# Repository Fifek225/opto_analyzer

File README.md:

This is a project of a RaspberryPi Pico expander board for Optical power measurements.
SFP connector acts as a receiver (analysis) and transmitter (test signals) of optical impulses.
External attenuators can be used to "play" with the power level.

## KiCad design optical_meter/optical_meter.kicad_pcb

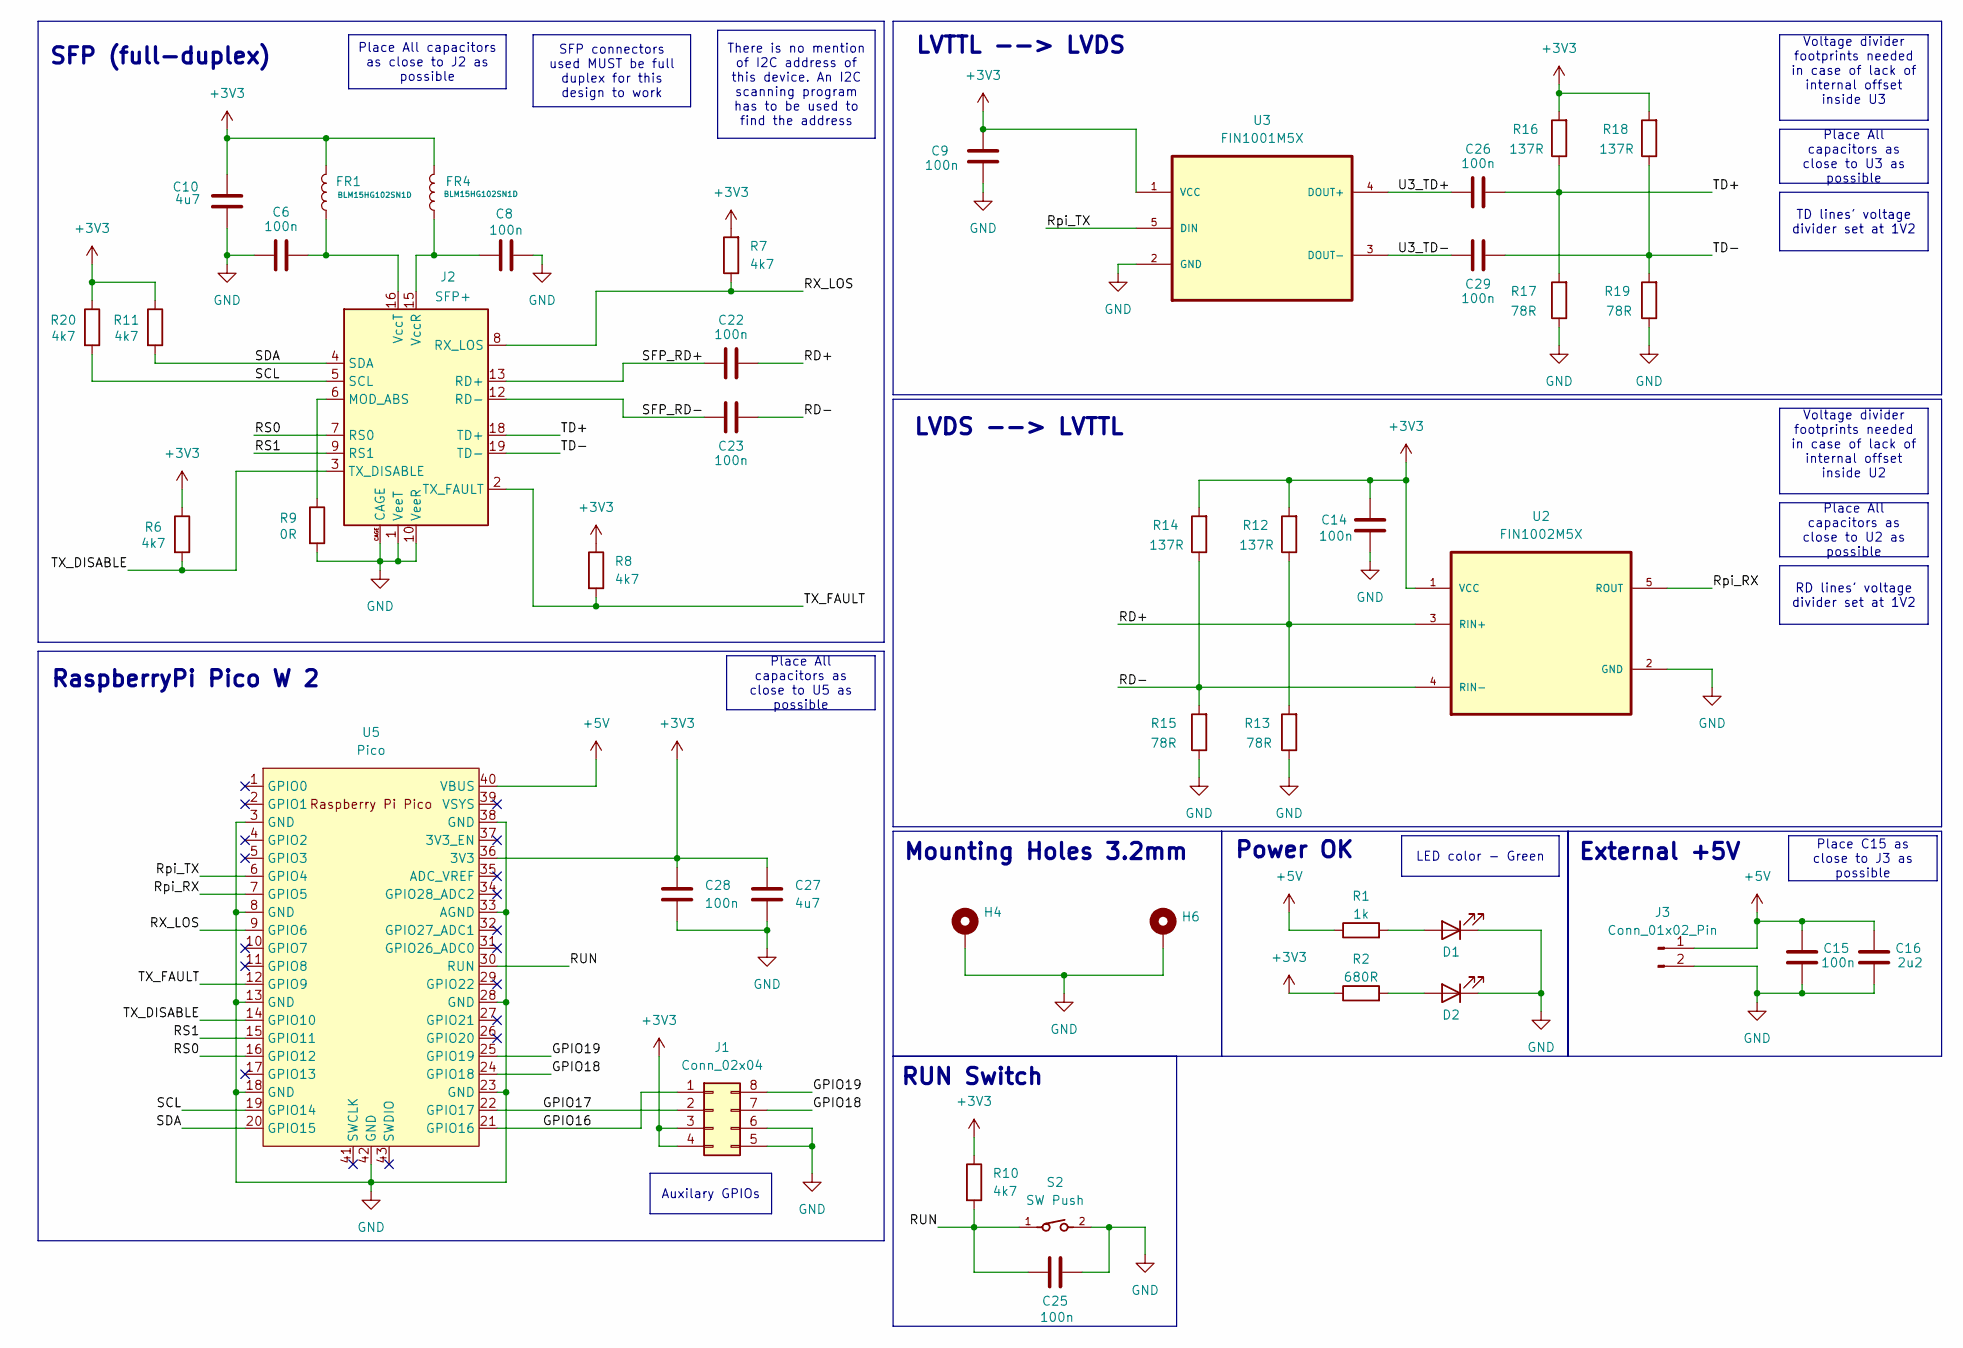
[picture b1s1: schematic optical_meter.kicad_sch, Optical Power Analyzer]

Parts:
C6, C8, C9, C14, C15, C22, C23, C25, C26, C28, C29: 100n; C_0603_1608Metric
C10, C27: 4u7; C_0603_1608Metric
C16: 2u2; C_0603_1608Metric
D1, D2: LED; LED_0603_1608Metric_Pad1.05x0.95mm_HandSolder
FR1, FR4: BLM15HG102SN1D; L_0402_1005Metric_Pad0.77x0.64mm_HandSolder
H4, H6: MountingHole_3.2mm_M3_DIN965_Pad
J1: Conn_02x04; PinHeader_2x04_P2.54mm_Vertical
J2: SFP+; Connector_SFP_and_Cage
J3: Conn_01x02_Pin; PinHeader_1x02_P2.54mm_Vertical
R1: 1k; R_0603_1608Metric_Pad0.98x0.95mm_HandSolder
R2: 680R; R_0603_1608Metric_Pad0.98x0.95mm_HandSolder
R6, R7, R8, R10, R11, R20: 4k7; R_0603_1608Metric_Pad0.98x0.95mm_HandSolder
R9: 0R; R_0603_1608Metric_Pad0.98x0.95mm_HandSolder
R12, R14, R16, R18: 137R; R_0603_1608Metric_Pad0.98x0.95mm_HandSolder
R13, R15, R17, R19: 78R; R_0603_1608Metric_Pad0.98x0.95mm_HandSolder
S2: SW Push; 434123025816
U2: FIN1002M5X; SOT95P280X140-5N; MPN FIN1002M5X
U3: FIN1001M5X; SOT95P280X140-5N; MPN FIN1001M5X
U5: Pico; RPi_Pico_SMD_TH

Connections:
+3V3: C9.2, C10.2, C14.1, C27.1, C28.1, FR1.2, FR4.2, J1.3, J1.4, R2.1, R6.1, R7.2, R8.1, R10.1, R11.1, R12.2, R14.2, R16.2, R18.2, R20.1, U2.1 (VCC), U3.1 (VCC), U5.36 (3V3)
+5V: C15.1, C16.1, J3.1, R1.1, U5.40 (VBUS)
/GPIO16: J1.1, U5.21 (GPIO16)
/GPIO17: J1.2, U5.22 (GPIO17)
/GPIO18: J1.7, U5.24 (GPIO18)
/GPIO19: J1.8, U5.25 (GPIO19)
/RD+: C22.2, R12.1, R13.2, U2.3 (RIN+)
/RD-: C23.2, R14.1, R15.2, U2.4 (RIN-)
/RS0: J2.7 (RS0), U5.16 (GPIO12)
/RS1: J2.9 (RS1), U5.15 (GPIO11)
/RUN: C25.2, R10.2, S2.1, U5.30 (RUN)
/RX_LOS: J2.8 (RX_LOS), R7.1, U5.9 (GPIO6)
/Rpi_RX: U2.5 (ROUT), U5.7 (GPIO5)
/Rpi_TX: U3.5 (DIN), U5.6 (GPIO4)
/SCL: J2.5 (SCL), R20.2, U5.19 (GPIO14)
/SDA: J2.4 (SDA), R11.2, U5.20 (GPIO15)
/SFP_RD+: C22.1, J2.13 (RD+)
/SFP_RD-: C23.1, J2.12 (RD-)
/TD+: C26.2, J2.18 (TD+), R16.1, R17.2
/TD-: C29.2, J2.19 (TD-), R18.1, R19.2
/TX_DISABLE: J2.3 (TX_DISABLE), R6.2, U5.14 (GPIO10)
/TX_FAULT: J2.2 (TX_FAULT), R8.2, U5.12 (GPIO9)
/U3_TD+: C26.1, U3.4 (DOUT+)
/U3_TD-: C29.1, U3.3 (DOUT-)
GND: C6.1, C8.2, C9.1, C10.1, C14.2, C15.2, C16.2, C25.1, C27.2, C28.2, D1.1 (K), D2.1 (K), H4.1, H6.1, J1.5, J1.6, J2.1 (VeeT), J2.10 (VeeR), J2.11 (VeeR), J2.14 (VeeR), J2.17 (VeeT), J2.20 (VeeT), J2.CAGE, J3.2, R9.2, R13.1, R15.1, R17.1, R19.1, S2.2, U2.2 (GND), U3.2 (GND), U5.3 (GND), U5.8 (GND), U5.13 (GND), U5.18 (GND), U5.23 (GND), U5.28 (GND), U5.33 (AGND), U5.38 (GND), U5.42 (GND); also elsewhere on the board
unnamed: D1.2 (A), R1.2
unnamed: D2.2 (A), R2.2
unnamed: J2.6 (MOD_ABS), R9.1
unnamed: C8.1, FR4.1, J2.15 (VccR)
unnamed: C6.2, FR1.1, J2.16 (VccT)

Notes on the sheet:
RUN Switch
Power OK
External +5V
LVTTL --> LVDS
Mounting Holes 3.2mm
RaspberryPi Pico W 2
LVDS --> LVTTL
SFP (full-duplex)
TD lines' voltage divider set at 1V2
Place All capacitors as close to J2 as possible
Place All capacitors as close to U2 as possible
Voltage divider footprints needed in case of lack of internal offset inside U3
Place All capacitors as close to U5 as possible
There is no mention of I2C address of this device. An I2C scanning program has to be used to find the address
Voltage divider footprints needed in case of lack of internal offset inside U2
Place C15 as close to J3 as possible
Auxilary GPIOs
SFP connectors used MUST be full duplex for this design to work
LED color - Green
Place All capacitors as close to U3 as possible
RD lines' voltage divider set at 1V2

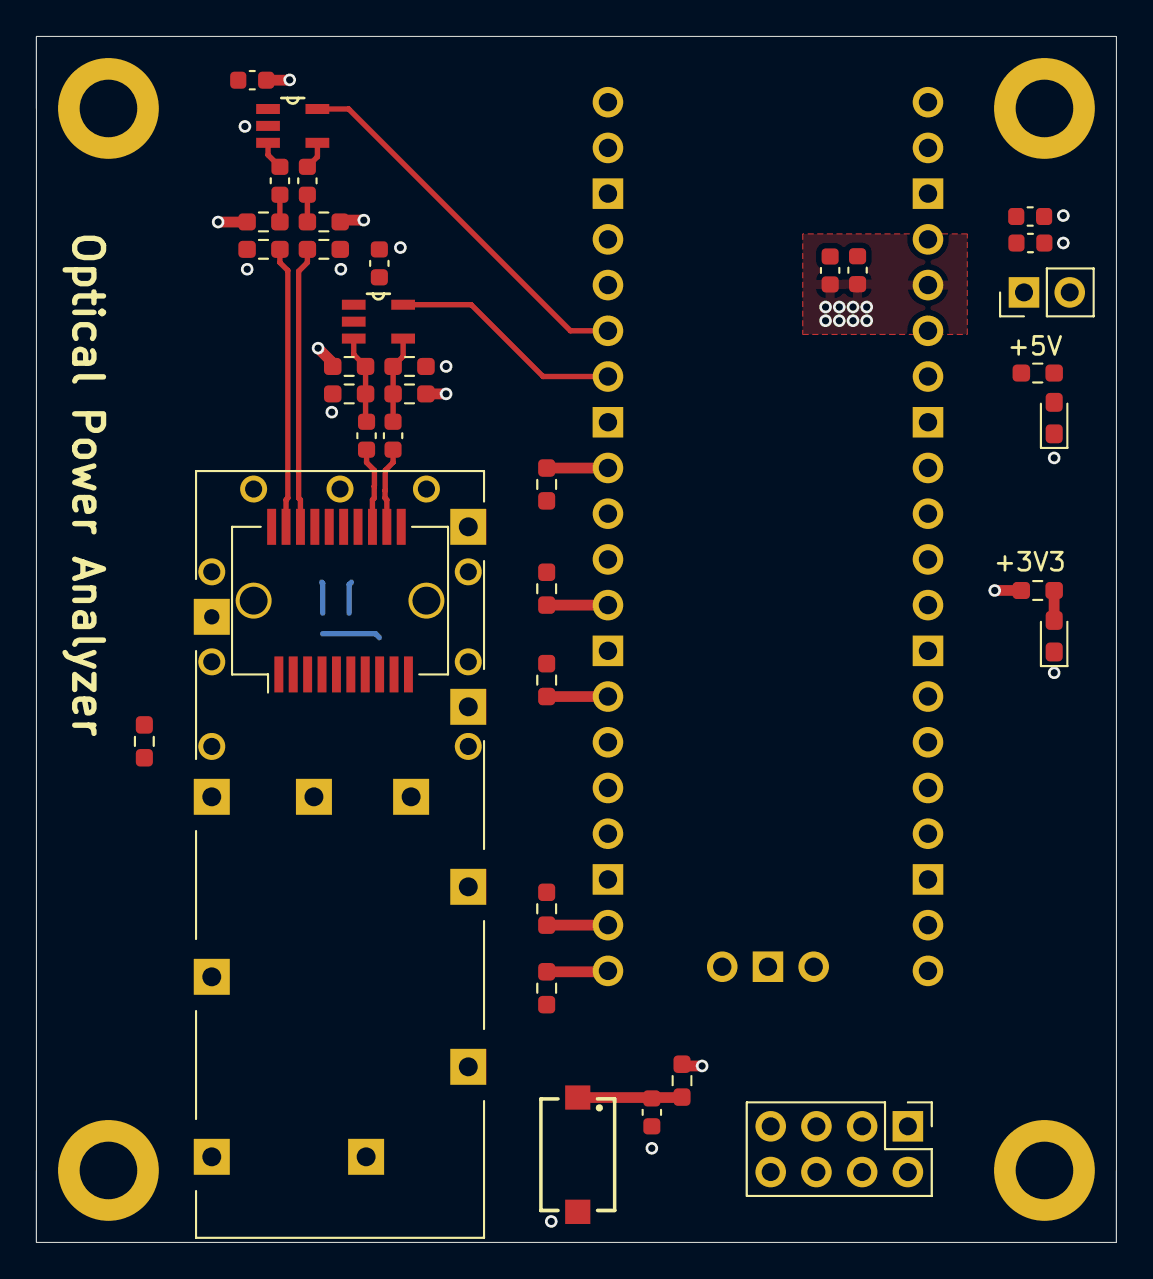
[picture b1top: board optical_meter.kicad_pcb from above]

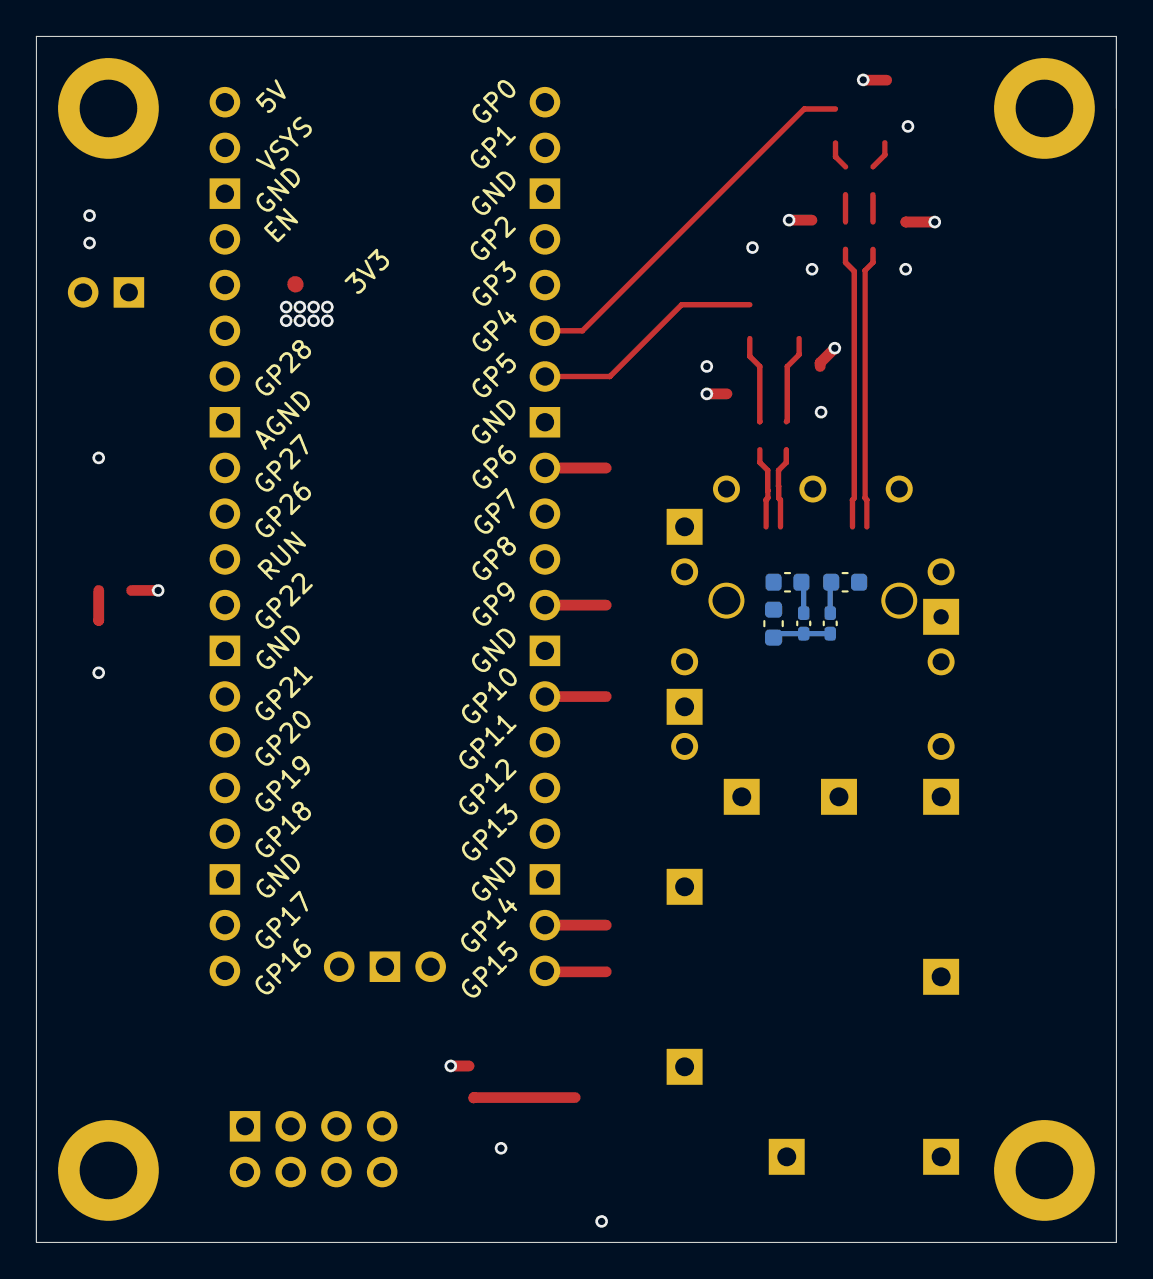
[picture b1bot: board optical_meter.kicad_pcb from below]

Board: 4 copper layers, 60.0 x 67.0 mm, 46 parts (5 on the bottom side), 30 nets.

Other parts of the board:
H4#2, H6#2: MountingHole_3.2mm_M3_DIN965_Pad

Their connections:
GND: H4#2.1, H6#2.1; also elsewhere on the board

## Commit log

2025-04-03 Creating KiCad 9.0 project of the PCB, adding gitignore and README files
2025-04-05 Adding MH, Power OK diodes, new Goldping socket 3D model for RaspPi, SFP connectors with cage 3D model
2025-04-07 Finished schematic (v1.0)
2025-04-07 Fixed pullup connections at TX_FAULT and R_LOS pins
2025-04-07 Adding voltage divider bias for +1V2 at RD1 pins of component U2
2025-04-07 Removing 100R termination Resistor R9 from TD0 lines
2025-04-07 Added review notes regards Root page
2025-04-07 Adding components to PCB
2025-04-07 Cosmetic changes to schematic - GND downwards, power rails upwards
2025-04-08 Removing Global labels for power nets
2025-04-08 Cosmetic changes to schematic sheet
2025-04-11 Removing one SFP connector - now the PCB will only work with full-duplex SFP/SFT+ connectors. Also did a major schematic cleanup: no hierarchal design, added 2 more GPIOs, DNP voltage dividers on LVD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
2025-04-11 Created separate folder for all the schematic + footprint libs
2025-04-11 Fixing some 3D model file paths
2025-04-14 Defining PCB design rules. Adding net class for differential LVDSpairs with necessary calculations made
2025-04-14 fixing accidental short of GND to 3v3
2025-04-15 starting to place components on the PCB
2025-04-17 Finished layout. DRC passed except for courtyard and some footprint-schematic relaitions from KiCad that do not matter
2025-04-17 Updating readme
2025-04-24 changing the layout (in progress)
